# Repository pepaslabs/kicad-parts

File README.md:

# KiCADParts

A collection of KiCAD schematic symbols and component footprints which I have created / tweaked / used.

# Design Constraints / Preferred Values / Conventions

* Label size X / size Y / thickness ratio: 1 / 1 / 0.2

## Eeschema

Pins:

Field reference and component name:

Part outlines:

Specify a line width of zero for the default line width (same width as the pins):

## Pcbnew

* Large component value label (size X / size Y / thickness): 0.04" / 0.04" / 0.008"
* Common component value label (size X / size Y / thickness): 0.03" / 0.03" / 0.006"
* Minimum component value label (size X / size Y / thickness): 0.025" / 0.025" / 0.005"

* Outline thickness: 0.010"

## Pads

* Ratios:
 * **_A_**: Size X: 1, Size Y: 1, Offset Y: 0
 * **_B_**: Size X: 1, Size Y: 1.5, Offset Y: 0.25
 * **_C_**: Size X: 1, Size Y: 2, Offset Y: 0

### 0.060" nominal pads

Pads sized just under 0.060" (allows routing a 0.020" trace without violating DRC).

 * **_059A_**: Size X: 0.059", Size Y: 0.059", Offset Y: 0
 * **_059B_**: Size X: 0.059", Size Y: 0.0885", Offset Y: 0.01475"
 * **_059C_**: Size X: 0.059", Size Y: 0.118", Offset Y: 0

Drill size is 0.032" (the KiCAD default), which is used for:
 * 1/4W resistors
 * small signal diodes (e.g. 1N4148)
 * ceramic and small electrolytic capacitors
 * DIP leads
 * TO-92 leads

### 0.070" nominal pads

Pads sized just under 0.070" (allows routing a 0.010" trace without violating DRC).

 * **_069A_**: Size X: 0.069", Size Y: 0.069", Offset Y: 0
 * **_069B_**: Size X: 0.069", Size Y: 0.1035", Offset Y: 0.01725"
 * **_069C_**: Size X: 0.069", Size Y: 0.138", Offset Y: 0

Drill size is 0.040", which is used for:
 * 1/2W resistors
 * 1 Amp diodes (e.g. 1N4001)
 * TO-220 leads

### 0.080" nominal pads

Pads sized just under 0.080" (does not allow routing traces).

 * **_079A_**: Size X: 0.079", Size Y: 0.079", Offset Y: 0
 * **_079B_**: Size X: 0.079", Size Y: 0.1185", Offset Y: 0.01975"
 * **_079C_**: Size X: 0.079", Size Y: 0.158", Offset Y: 0

Drill size is 0.056", which is used for:
 * TO-218 leads
 * TO-247 leads
 * 3 Amp diodes (e.g. 1N5401)
 * 6 Amp diodes (e.g. 6A05)

## Naming Conventions

* All files (*.lib, *.dcm, *.mod) shall be prefixed with PL_
  * e.g. PL_diodes.lib 
* All footprint names shall be suffixed with _PL
  * e.g. TO-220_PL 

# PL_diodes.lib
(and PL_diodes.dcm)

* DIODE

* SCHOTTKY

* ZENER

# PL_diodes.mod

* DIODE_SS_059_PL
  * Small signal diode footprint
    * e.g. 1N4148, 1N5711

* DIODE_1A_069_PL
  * 1 Amp diode footprint
    * e.g. 1N4001, 1N5817

## Footprints

## License

Parts which I have created are released under the [MIT License](http://opensource.org/licenses/MIT).  Parts which I have modified are subject to their original license.

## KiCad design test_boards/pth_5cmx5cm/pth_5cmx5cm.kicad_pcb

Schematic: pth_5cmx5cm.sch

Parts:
H101, H102, H103, H104: HOLE
Q101: BC560
Q102: 2N3904
R101: 100k
R201: 4k7
U101: 4N35; DIP6

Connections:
GND: Q102.1 (E), R201.2, U101.4
unnamed: U101.2, U101.5
unnamed: Q101.1 (C), Q102.3 (C), U101.6
unnamed: Q102.2 (B), R101.2
unnamed: Q101.2 (B), R101.1
unnamed: Q101.3 (E), R201.1, U101.1

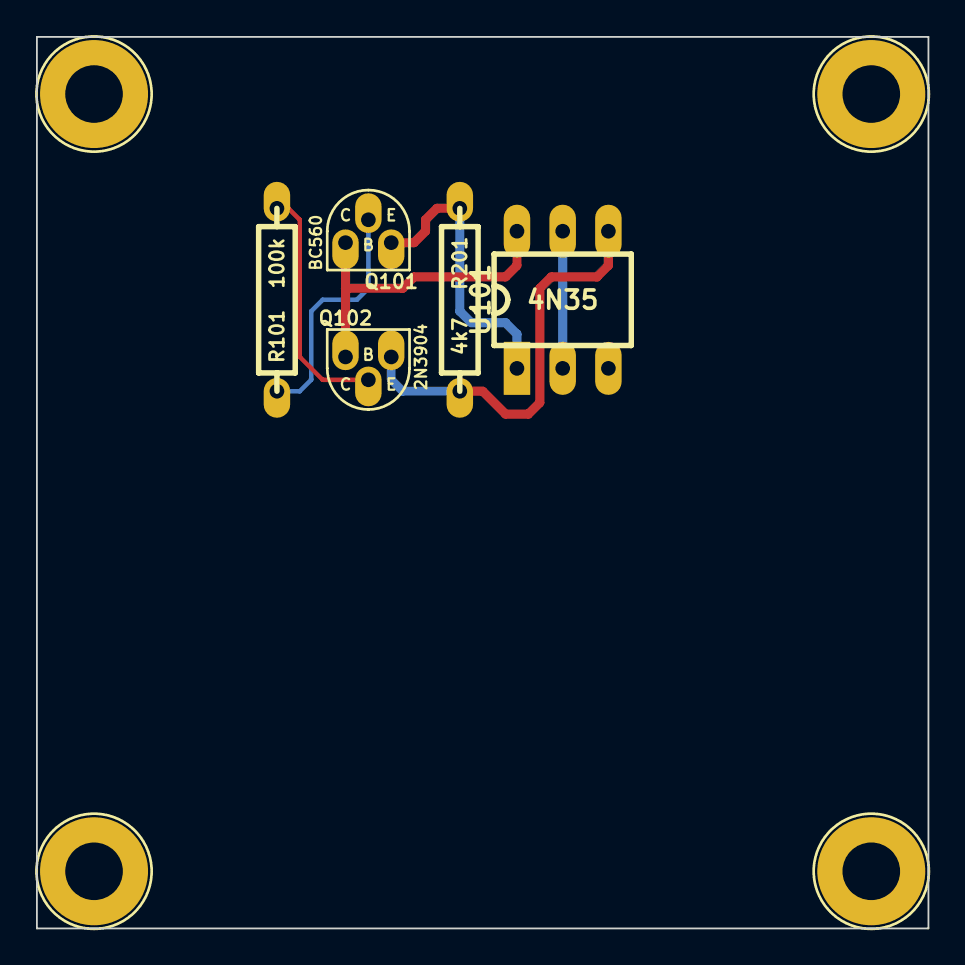
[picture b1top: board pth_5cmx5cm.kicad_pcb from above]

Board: 2 copper layers, 49.5 x 49.5 mm, 9 parts (0 on the bottom side), 6 nets.

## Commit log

2014-03-02 adding through-hole resistor symbols and footprints
2014-03-02 adding basic TO-92 transistors
2014-03-02 updating TO-92 with standard pad size, text size, and standard text values.
2014-03-02 tweaking resistor footprint text size
2014-03-02 creating test board file.
2014-03-02 adding DIP footprints
2014-03-02 increasing pad side of transistor footprints
2014-03-02 increasing resistor pad size.
2014-03-02 tweaking resistor text size to allow for three-digit reference designator naming.
2014-03-02 updating test board.
2014-03-02 adding mounting hole footprint, updating test board.
2014-03-02 saving project
2014-03-02 updating DIP footprints. adding opto library.
2014-03-02 moving files around
2014-03-02 updating test board (trying out tweaked pad settings)
2014-03-02 using new pad sizes
2014-03-02 updating test board
2014-03-02 pulling in OSHW-logo.mod (can't remember where I downloaded this from now...), reducing the number of logo options, and fixing the layers for the rest of the logos. updating demo board.
2014-03-03 adding relay symbols
2014-03-03 adding relay footprint for OMRON G5LA-1.
2014-03-13 adding heatsink footprint
2014-03-13 adding another heatsink footprint, with vent drills.
2014-03-15 adding module for single pads.
2014-03-15 updating parts for consistency (center on pin 1, etc)
2014-03-15 more positioning tweaks
2014-03-15 adding "gallery" schematic and layout.
2014-03-15 adding screenshots
2014-03-15 adding pads footprint to demo all pad sizes
2014-03-15 updating pads drill sizing and screenshots
2014-03-15 adding combo footprint for to-220, to-218, and to-247
2014-03-15 tweaking pads
2014-03-15 correcting mistake in relay schematic and footprint (datasheet was bottom view, not top view).
2014-03-15 layout tweaks for screenshots
2014-03-15 updating screenshots
2014-03-17 adding displays and updating switches
2014-03-17 tweaking relays, adding dc barrel jacks
2014-03-17 updating switches_PL
2014-03-17 adding capacitors and regulators.
2014-03-17 adding LED
2014-03-17 pulling in updated parts from DualLM317 project
2014-03-20 adding regulators and displays
2014-03-23 updating M3 mounting hole
2014-03-23 adding vertical resistor. adding 2.5x5.5mm barrel jack.
2014-03-23 adding banana jack
2014-03-23 updating resistor footprint filters
2014-03-23 adding 1/2 watt resistor footprint
2014-03-23 updating footprint filter
2014-03-23 font tweak
2014-03-23 updating footprint filters
2014-03-23 updating gallery schematic
2014-03-23 tweaking caps
2014-03-23 adding polarity to caps
2014-03-23 adding mini toggle switch
2014-03-23 updating connectors and swithes footprints
2014-03-23 adding diodes
2014-03-23 adding potentiometer symbols
2014-03-23 adding potentiometers
2014-03-23 adding volt meter
2014-03-23 updating displays
2014-03-24 adding ebay ammeter footprint
2014-03-26 updating 1pin
2014-03-28 pulling in updated parts from lm317 project.
2014-04-20 adding 7812 regulator. updating line thickness of to-220 footprints.
2014-04-21 updating 10 turn pot footprint
2014-04-21 updating footprint for ebay ammeter
2014-04-21 updating voltmeter footprint
2014-04-21 narrowing drills on barrell back footprints
2014-05-04 adding XR-2206
2014-05-04 updating XR-2206 symbol layout
2014-05-04 tweaking placement of potentiometer fields
2014-05-04 adding film capacitor.
2014-05-04 updating gallery
2014-06-04 pulling in 4P4C connector and symbol.
2014-06-04 adding additional 4P4C footprint.
2014-06-19 updating DIP8 footprints.
2014-06-19 updating more footprints
2014-06-30 updating telephone jack connectors.
2014-06-30 adding 8P8C connector.
2014-07-04 adding in opamps lib.
2014-07-06 adding inductors and references.
2014-07-06 making a SOT-23-5 with longer legs
2014-07-06 tweaking label positions for toggle switch.
2014-07-06 adding inductors.
2014-07-06 updating LED pads
2014-07-06 adding drill holes to reach calibration potentiometer on voltmeter display.
2014-07-06 pulling in updated files.
2014-07-09 pulling in updated parts.
2015-03-23 pulling in updated parts from another project.
2015-04-02 creating 2-terminal and 3-terminal blocks.
2015-04-11 updating diodes lib
2015-04-11 pulling in screenshot
2015-04-11 removing old diode files
2015-04-11 updating footprint filters and descriptions
2015-04-11 updating diodes footprint
2015-04-11 creating example projects for diode parts.
2015-04-11 adding screenshot
2015-04-11 removing backup files
2015-05-22 pulling in updated parts
2017-04-11 renaming files, merging opamp libs
2017-04-11 renaming files
2017-04-11 merging voltage reference libs
2017-04-11 pulling in resistors
2017-04-12 updating footprint list for caps
2017-04-12 updating inductors lib
2017-04-12 updating opamp lib
2017-04-12 updating opto lib
2017-04-12 updating regulators lib
2017-04-12 updating switches and switchers libs
2017-04-12 updating transistors.lib
2017-04-13 updating SMD DIL module
2017-04-13 reverting transistors lib
2017-04-13 updating dcm files
2017-04-13 file organization
2017-04-13 cleanup
2017-04-13 updating caps
2017-04-13 updating resistors
2017-04-13 updating diodes, regulartors, opamps
2017-04-13 updating regulators
2017-04-13 updating opamps and transistors
2017-04-22 updating opamps
2017-04-23 updating switch schematic
2017-05-10 updating microcontrollers
2017-05-10 screenshots
2017-05-10 GPIB
2017-05-10 GPIB connector
2017-05-10 updating connectors
2017-05-13 updating connectors and opamps
2017-05-21 updating TO-46
2017-06-01 adding EC2 Kemet relay
2017-06-01 adding GPIB connector
2017-06-01 updating comms
2017-06-12 updating parts
2017-07-02 adding SP12T switch
2017-07-02 adding LT6657
2017-09-03 more parts
2017-09-09 more parts updates
2017-12-27 wider drill for 1 amp diodes
2017-12-28 updating text size on diodes
2018-02-15 parts
2018-02-25 regulators
2018-03-08 VRE3050
2018-04-29 pulling in updated TO-99
2018-04-29 machine pin header
2018-04-29 removing 2nd machine pin option
2018-06-27 updated parts
2018-07-02 LM723
2018-07-06 lm723 fix
2018-07-06 part updates
2020-09-28 LM311
2020-10-14 adding dual-gang pot, trs 3.5mm jack, npn
2020-10-14 footprint filter
2020-10-14 ferrite core
2020-10-14 3.5mm TRS jack
2020-10-16 adding potentiometer
2020-10-24 misc updates
2020-10-24 more part updates
2020-10-28 more updated parts
2020-10-29 narrower pad DIP-16
2020-10-29 another DIP footprint
2020-10-31 relay fix
2020-11-14 555 timer and 12-position switch
2020-11-14 using PL_ prefix in PL_1pin.mod
2020-11-14 using PL_ prefix in PL_capacitors.mod
2020-11-14 more PL_ prefixes for .mod file parts
2020-11-14 using PL_ prefix on all parts
2020-11-14 bugfix
2020-11-14 mcx and mmcx
2020-11-14 0.1 capacitor footprint
2020-11-14 ZIF socket
2020-11-18 fixing pinout of TL431
2020-11-18 oops
2020-11-23 adding PNP BCE
2020-11-23 adding 7414 hex inverters and smaller diode footprint
2020-11-28 fixing a switch footprint
2022-06-20 adding pro micro
2022-08-30 sza263
2022-09-02 ad587-stick
